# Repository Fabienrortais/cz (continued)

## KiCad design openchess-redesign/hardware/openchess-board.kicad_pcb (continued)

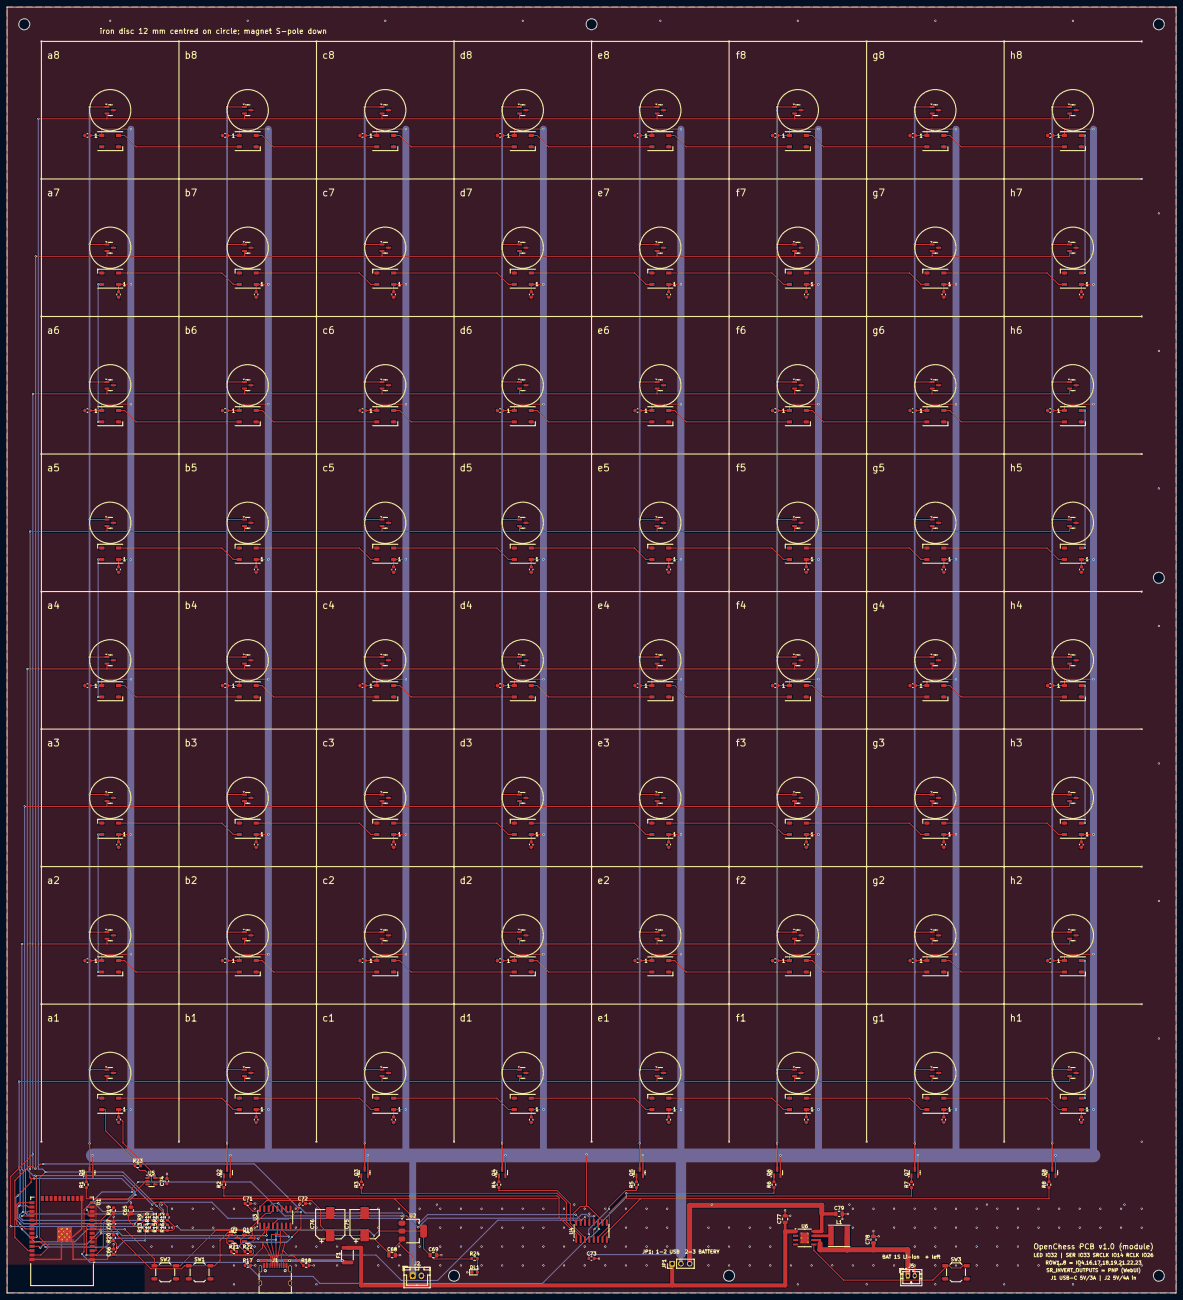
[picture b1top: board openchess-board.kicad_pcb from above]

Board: 2 copper layers, 340.0 x 374.0 mm, 263 parts (0 on the bottom side), 124 nets.

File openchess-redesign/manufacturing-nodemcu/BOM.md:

# Bill of materials (generated by tools/export.py)

| Qty | Designators | Value | MPN / note | Footprint | LCSC | Description |
|---|---|---|---|---|---|---|
| 64 | H1..H64 (64) | HX3144ESO | HX3144ESO | SOT-23 | TBD | Hall switch |
| 64 | D1..D64 (64) | WS2812B | WS2812B-B/T | LED_WS2812B_PLCC4_5.0x5.0mm_P3.2mm | C2761795 | RGB LED |
| 64 | C1..C64 (64) | 100nF | CL10B104KB8NNNC | C_0603_1608Metric | C14663 | LED decoupling |
| 1 | J3 | DEV_TOP | 1x19 female header 2.54 mm | PinSocket_1x19_P2.54mm_Vertical | TBD | Dev board socket, top row (GND,23,22,TX,RX,21,GND,19,18,5,17,16,4,0,2,15,SD1,SD0,CLK) |
| 1 | J4 | DEV_BOTTOM | 1x19 female header 2.54 mm | PinSocket_1x19_P2.54mm_Vertical | TBD | Dev board socket, bottom row (3V3,EN,VP,VN,34,35,32,33,25,26,27,14,12,GND,13,SD2,SD3,CMD,5V) |
| 8 | R9..R16 (8) | 10k |  | R_0603_1608Metric | C25804 | ROW0 pull-up |
| 1 | U5 | 74AHCT1G125 | SN74AHCT1G125DBVR | SOT-23-5 | TBD | WS2812B data level shifter |
| 2 | C74,C73 | 100nF |  | C_0603_1608Metric | C14663 | U5 decoupling |
| 1 | R23 | 330 |  | R_0603_1608Metric | C23138 | LED data series |
| 1 | J1 | USB-C | TYPE-C-31-M-12 | USB_C_Receptacle_HRO_TYPE-C-31-M-12 | C165948 | USB-C receptacle 16P |
| 2 | R17,R18 | 5.1k |  | R_0603_1608Metric | C23186 | USB CC1 pull-down |
| 1 | F1 | 3A PTC | MF-MSMF300-2 / BSMD1812-300 | Fuse_1812_4532Metric | TBD | Resettable fuse 3A hold (USB path) |
| 1 | U6 | IP5306 | IP5306 | HSOP-8-1EP_3.9x4.9mm_P1.27mm_EP2.41x3.1mm_ThermalVias | C181692 | Li-ion charger (2.1 A) + 5 V boost (2.4 A), power-bank IC |
| 1 | L1 | 1uH 4A | NR6028T1R0N / CD63 1uH >=4A | L_Taiyo-Yuden_NR-60xx | TBD | Boost inductor 1 uH, >= 4 A sat, 6x6 mm |
| 3 | C77,C78,C79 | 22uF |  | C_0805_2012Metric | C45783 | IP5306 VIN cap |
| 1 | J5 | BATTERY | B2B-PH-K-S | JST_PH_B2B-PH-K_1x02_P2.00mm_Vertical | C131337 | 1S Li-ion / LiPo battery, JST-PH 2.0 mm (+ on pin 1, check your pack!) |
| 1 | JP1 | PWR SEL | 1x3 header + jumper | PinHeader_1x03_P2.54mm_Vertical | C2337 | Power select: 1-2 = USB direct (no battery), 2-3 = battery/boost (IP5306) |
| 1 | SW3 | PWR | TS-1187A-B-A-B | SW_SPST_TL3342 | C318884 | IP5306 KEY: short press = boost on, long press = off |
| 1 | J2 | 5V IN | B2B-XH-A | JST_XH_B2B-XH-A_1x02_P2.50mm_Vertical | C158012 | External 5V/4A input (optional, bypasses fuse) |
| 2 | C75,C76 | 470uF 10V | 470uF/10V SMD 8x10 | CP_Elec_8x10 | TBD | 5V bulk capacitor |
| 1 | DL1 | PWR |  | LED_0603_1608Metric | C72043 | Power LED (green) |
| 9 | R24..R8 (9) | 1k |  | R_0603_1608Metric | C21190 | Power LED series |
| 1 | U4 | 74HCT595 | SN74HCT595DR / 74HCT595D | SOIC-16_3.9x9.9mm_P1.27mm | TBD | Column shift register (HCT = 3.3V-input compatible) |
| 8 | Q1..Q8 (8) | S8550 | S8550 | SOT-23 | C2150 | Column a high-side PNP switch |

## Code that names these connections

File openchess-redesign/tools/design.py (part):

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                      pins={"1": "+3V3", "2": "GND"}, x=124.0, y=H - 11.0, rot=0, lcsc="C15850", desc="LDO output"))
        # USB-serial bridge + auto-reset (DevKitC circuit)
        P.append(Part(ref="U3", symbol="Interface_USB:CH340C", footprint="Package_SO:SOIC-16_3.9x9.9mm_P1.27mm", value="CH340C",
                      pins={"1": "GND", "2": "TXD0_U", "3": "RXD0_U", "4": "CH_V3", "5": "USB_D+", "6": "USB_D-", "7": "NC_U3_7",
                            "8": "NC_U3_8", "9": "NC_U3_9", "10": "NC_U3_10", "11": "NC_U3_11", "12": "NC_U3_12",
                            "13": "DTR", "14": "RTS", "15": "NC_U3_15", "16": "+5V"},
                      x=78.0, y=H - 22.0, rot=90, lcsc="C84681", mpn="CH340C", desc="USB to UART (no crystal needed)"))
        P.append(Part(ref="C71", symbol="Device:C", footprint="Capacitor_SMD:C_0603_1608Metric", value="100nF",
                      pins={"1": "+5V", "2": "GND"}, x=70.0, y=H - 26.0, rot=0, lcsc="C14663", desc="CH340 VCC decoupling"))
        P.append(Part(ref="C72", symbol="Device:C", footprint="Capacitor_SMD:C_0603_1608Metric", value="100nF",
                      pins={"1": "CH_V3", "2": "GND"}, x=86.0, y=H - 26.0, rot=0, lcsc="C14663", desc="CH340 V3 decoupling"))
        P.append(Part(ref="Q9", symbol="Transistor_BJT:MMBT3904", footprint="Package_TO_SOT_SMD:SOT-23", value="S8050",
                      pins={"1": "DTR_R", "2": "RTS", "3": "EN"}, x=66.0, y=H - 16.0, rot=0, lcsc="C2146", mpn="S8050 J3Y (NPN)", desc="Auto-reset"))
        P.append(Part(ref="Q10", symbol="Transistor_BJT:MMBT3904", footprint="Package_TO_SOT_SMD:SOT-23", value="S8050",
                      pins={"1": "RTS_R", "2": "DTR", "3": "IO0"}, x=70.0, y=H - 16.0, rot=0, lcsc="C2146", mpn="S8050 J3Y (NPN)", desc="Auto-boot"))
        P.append(Part(ref="R21", symbol="Device:R", footprint="Resistor_SMD:R_0603_1608Metric", value="10k",
                      pins={"1": "DTR", "2": "DTR_R"}, x=66.0, y=H - 12.0, rot=0, lcsc="C25804", desc="Auto-reset base"))
        P.append(Part(ref="R22", symbol="Device:R", footprint="Resistor_SMD:R_0603_1608Metric", value="10k",
                      pins={"1": "RTS", "2": "RTS_R"}, x=70.0, y=H - 12.0, rot=0, lcsc="C25804", desc="Auto-boot base"))
        usb_dp, usb_dm = "USB_D+", "USB_D-"
        row_pullup_y = (Ys + 20.0, Ys + 23.0)
    else:
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
    # LED data level shifter 3.3V -> 5V
    P.append(Part(ref="U5", symbol="74xGxx:74AHCT1G125", footprint="Package_TO_SOT_SMD:SOT-23-5", value="74AHCT1G125",
                  pins={"1": "GND", "2": "IO32", "3": "GND", "4": "LED_DATA_5V", "5": "+5V"},
                  x=42.0, y=Ys + 9.5, rot=0, lcsc="C7484", mpn="SN74AHCT1G125DBVR", desc="WS2812B data level shifter"))
    P.append(Part(ref="C74", symbol="Device:C", footprint="Capacitor_SMD:C_0603_1608Metric", value="100nF",
                  pins={"1": "+5V", "2": "GND"}, x=46.5, y=Ys + 9.5, rot=90, lcsc="C14663", desc="U5 decoupling"))
    P.append(Part(ref="R23", symbol="Device:R", footprint="Resistor_SMD:R_0603_1608Metric", value="330",
                  pins={"1": "LED_DATA_5V", "2": "LED_DATA"}, x=38.0, y=Ys + 5.0, rot=0, lcsc="C23138", mpn="330R 0603 (verify C23138)", desc="LED data series"))

    # Power input: USB-C (5V/3A) + optional external 5V, polyfuse, bulk caps
    P.append(Part(ref="J1", symbol="Connector:USB_C_Receptacle_USB2.0_16P",
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    P.append(Part(ref="R18", symbol="Device:R", footprint="Resistor_SMD:R_0603_1608Metric", value="5.1k",
                  pins={"1": "CC2", "2": "GND"}, x=87.0, y=H - 8.0, rot=0, lcsc="C23186", desc="USB CC2 pull-down"))
    P.append(Part(ref="F1", symbol="Device:Polyfuse", footprint="Fuse:Fuse_1812_4532Metric", value="3A PTC",
                  pins={"1": "VBUS", "2": "VUSB5" if BATTERY else "+5V"}, x=99.0, y=H - 11.0, rot=90, lcsc="C883162",
                  mpn="BSMD1812-300-16V (BHFUSE) or ASMD1812-300 C135366", desc="Resettable fuse 3A hold (USB path)"))
    if BATTERY:
        # IP5306: 5 V in -> charges a 1S Li-ion; boosts the battery to 5 V / 2.4 A on VOUT. JP1 selects the bus source.
        P.append(Part(ref="U6", symbol="OpenChess:IP5306", footprint="Package_SO:HSOP-8-1EP_3.9x4.9mm_P1.27mm_EP2.41x3.1mm_ThermalVias",
                      value="IP5306", pins={"1": "VUSB5", "2": "NC_LED1", "3": "NC_LED2", "4": "NC_LED3", "5": "KEY", "6": "BAT",
                                            "7": "LX", "8": "VBOOST", "9": "GND"},
                      x=232.0, y=H - 16.0, rot=0, lcsc="C181692", mpn="IP5306", desc="Li-ion charger (2.1 A) + 5 V boost (2.4 A), power-bank IC"))
        P.append(Part(ref="L1", symbol="Device:L", footprint="Inductor_SMD:L_Taiyo-Yuden_NR-60xx", value="1uH 4A",
                      pins={"1": "LX", "2": "BAT"}, x=242.0, y=H - 16.6, rot=0, lcsc="C96955", mpn="SWPA6045S1R0NT (Sunlord) / CKCS6045-1uH/N C354627 / NR6045T1R0N - check land pattern",
                      desc="Boost inductor 1 uH, >= 4 A sat, 6x6 mm"))
        P.append(Part(ref="C77", symbol="Device:C", footprint="Capacitor_SMD:C_0805_2012Metric", value="22uF",
                      pins={"1": "VUSB5", "2": "GND"}, x=226.3, y=H - 21.5, rot=90, lcsc="C45783", desc="IP5306 VIN cap"))
        P.append(Part(ref="C78", symbol="Device:C", footprint="Capacitor_SMD:C_0805_2012Metric", value="22uF",
                      pins={"1": "BAT", "2": "GND"}, x=252.0, y=H - 15.5, rot=90, lcsc="C45783", desc="IP5306 BAT cap"))
        P.append(Part(ref="C79", symbol="Device:C", footprint="Capacitor_SMD:C_0805_2012Metric", value="22uF",
                      pins={"1": "VBOOST", "2": "GND"}, x=242.0, y=H - 23.0, rot=0, lcsc="C45783", desc="IP5306 VOUT cap"))
        P.append(Part(ref="J5", symbol="Connector_Generic:Conn_01x02", footprint="Connector_JST:JST_PH_B2B-PH-K_1x02_P2.00mm_Vertical",
                      value="BATTERY", pins={"1": "BAT", "2": "GND"}, x=262.0, y=H - 5.0, rot=0, lcsc="C131337", mpn="B2B-PH-K-S",
                      desc="1S Li-ion / LiPo battery, JST-PH 2.0 mm (+ on pin 1, check your pack!)"))
        P.append(Part(ref="JP1", symbol="Connector_Generic:Conn_01x03", footprint="Connector_PinHeader_2.54mm:PinHeader_1x03_P2.54mm_Vertical",
                      value="PWR SEL", pins={"1": "VUSB5", "2": "+5V", "3": "VBOOST"}, x=193.46, y=H - 8.5, rot=90, lcsc="",
                      mpn="1x3 pin header 2.54 mm + jumper cap", desc="Power select: 1-2 = USB direct (no battery), 2-3 = battery/boost (IP5306)"))
        P.append(Part(ref="SW3", symbol="Switch:SW_Push", footprint="Button_Switch_SMD:SW_SPST_TL3342", value="PWR",
                      pins={"1": "KEY", "2": "GND"}, x=276.0, y=H - 6.0, rot=0, lcsc="C318884", mpn="TS-1187A-B-A-B",
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                  pins={"1": "+5V", "2": "GND"}, x=94.0, y=H - 20.0, rot=90, lcsc="C3341", mpn="RVT1C471M0810 470uF 16V D8xL10 (verify)",
                  desc="5V bulk capacitor"))
    P.append(Part(ref="DL1", symbol="Device:LED", footprint="LED_SMD:LED_0603_1608Metric", value="PWR",
                  pins={"1": "GND", "2": "PWRLED"}, x=136.0, y=H - 6.0, rot=0, lcsc="C72043", desc="Power LED (green)"))
    P.append(Part(ref="R24", symbol="Device:R", footprint="Resistor_SMD:R_0603_1608Metric", value="1k",
                  pins={"1": "+3V3", "2": "PWRLED"}, x=136.0, y=H - 10.0, rot=0, lcsc="C21190", desc="Power LED series"))

    # Column drivers: 74HCT595 + 8x (1k + PNP high-side switch), one PNP under each column
    P.append(Part(ref="U4", symbol="74xx:74HCT595", footprint="Package_SO:SOIC-16_3.9x9.9mm_P1.27mm", value="74HCT595",
                  pins={"1": "SRQ1", "2": "SRQ2", "3": "SRQ3", "4": "SRQ4", "5": "SRQ5", "6": "SRQ6", "7": "SRQ7",
                        "8": "GND", "9": "NC_U4_9", "10": "+5V", "11": "IO14", "12": "IO26", "13": "GND",
                        "14": "IO33", "15": "SRQ0", "16": "+5V"},
                  x=170.0, y=H - 18.0, rot=90, lcsc="C70468", mpn="74HCT595D,112 (Nexperia)", desc="Column shift register (HCT = 3.3V-input compatible)"))
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
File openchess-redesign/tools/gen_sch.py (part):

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                 S(sym("stroke"), S(sym("width"), 0.254), S(sym("type"), sym("default"))),
                 S(sym("fill"), S(sym("type"), sym("background"))))),
             S(sym("symbol"), "IP5306_1_1",
               pin("power_in", -10.16, 5.08, 0, "VIN", "1"), pin("open_collector", -10.16, 2.54, 0, "LED1", "2"),
               pin("open_collector", -10.16, 0, 0, "LED2", "3"), pin("open_collector", -10.16, -2.54, 0, "LED3", "4"),
               pin("input", 10.16, -5.08, 180, "KEY", "5"), pin("passive", 10.16, 0, 180, "BAT", "6"),
               pin("passive", 10.16, 2.54, 180, "L1", "7"), pin("power_out", 10.16, 5.08, 180, "VOUT", "8"),
               pin("power_in", 0, -11.43, 90, "GND", "9")))

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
